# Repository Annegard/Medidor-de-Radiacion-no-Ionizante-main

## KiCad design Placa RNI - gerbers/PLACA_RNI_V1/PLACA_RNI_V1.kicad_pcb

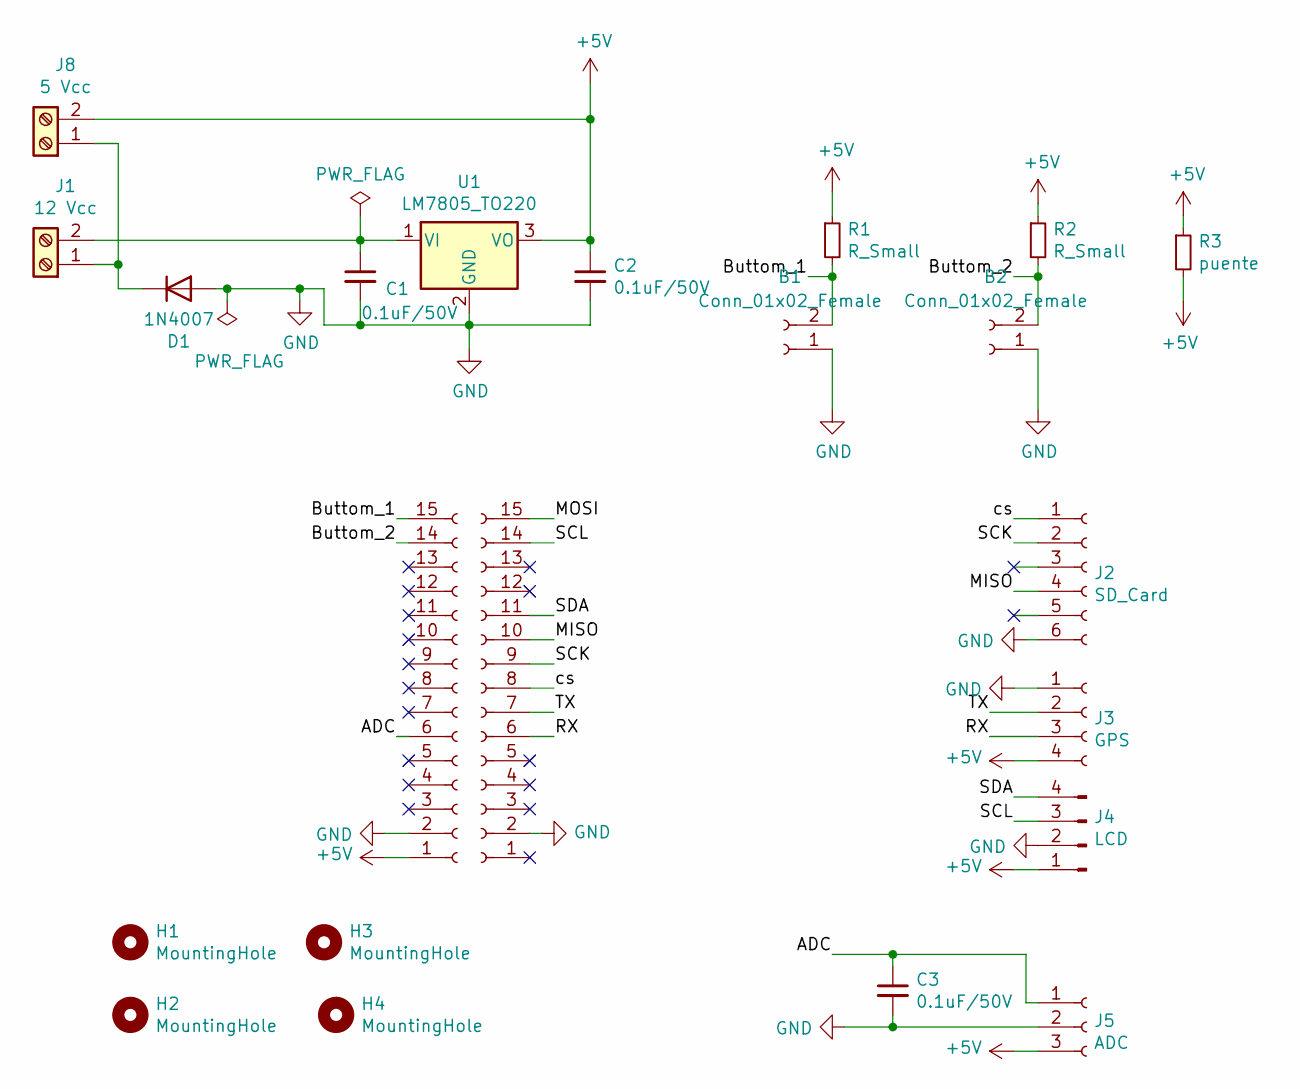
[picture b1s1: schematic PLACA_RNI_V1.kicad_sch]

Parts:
B1, B2: Conn_01x02_Female; PinSocket_1x02_P2.54mm_Vertical
C1, C2, C3: 0.1uF/50V; C_Disc_D7.0mm_W2.5mm_P5.00mm
D1: 1N4007; D_DO-41_SOD81_P10.16mm_Horizontal
H1, H2, H3, H4: MountingHole; MountingHole_2.5mm
J1: 12 Vcc; TerminalBlock_bornier-2_P5.08mm
J2: SD_Card; PinHeader_1x06_P2.54mm_Vertical
J3: GPS; PinHeader_1x04_P2.54mm_Vertical
J4: LCD; PinHeader_1x04_P2.54mm_Vertical
J5: ADC; PinHeader_1x03_P2.54mm_Vertical
J6, J7: Conn_01x15_Female; PinSocket_1x15_P2.54mm_Vertical
J8: 5 Vcc; TerminalBlock_bornier-2_P5.08mm
R1, R2: R_Small; R_Axial_DIN0207_L6.3mm_D2.5mm_P10.16mm_Horizontal
R3: puente; R_Axial_DIN0207_L6.3mm_D2.5mm_P10.16mm_Horizontal
U1: LM7805_TO220; TO-220-3_Vertical

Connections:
+5V: C2.1, J3.4, J4.1, J5.3, J6.1, J8.2, R1.1, R2.1, R3.1, R3.2, U1.3 (VO)
/ADC: C3.1, J5.1, J6.6
/Buttom_1: B1.2, J6.15, R1.2
/Buttom_2: B2.2, J6.14, R2.2
/MISO: J2.4, J7.10
/MOSI: J7.15
/RX: J3.3, J7.6
/SCK: J2.2, J7.9
/SCL: J4.3, J7.14
/SDA: J4.4, J7.11
/TX: J3.2, J7.7
/cs: J2.1, J7.8
GND: B1.1, B2.1, C1.2, C2.2, C3.2, D1.2 (A), J2.6, J3.1, J4.2, J5.2, J6.2, J7.2, U1.2 (GND)
unnamed: C1.1, J1.2, U1.1 (VI)
unnamed: D1.1 (K), J1.1, J8.1

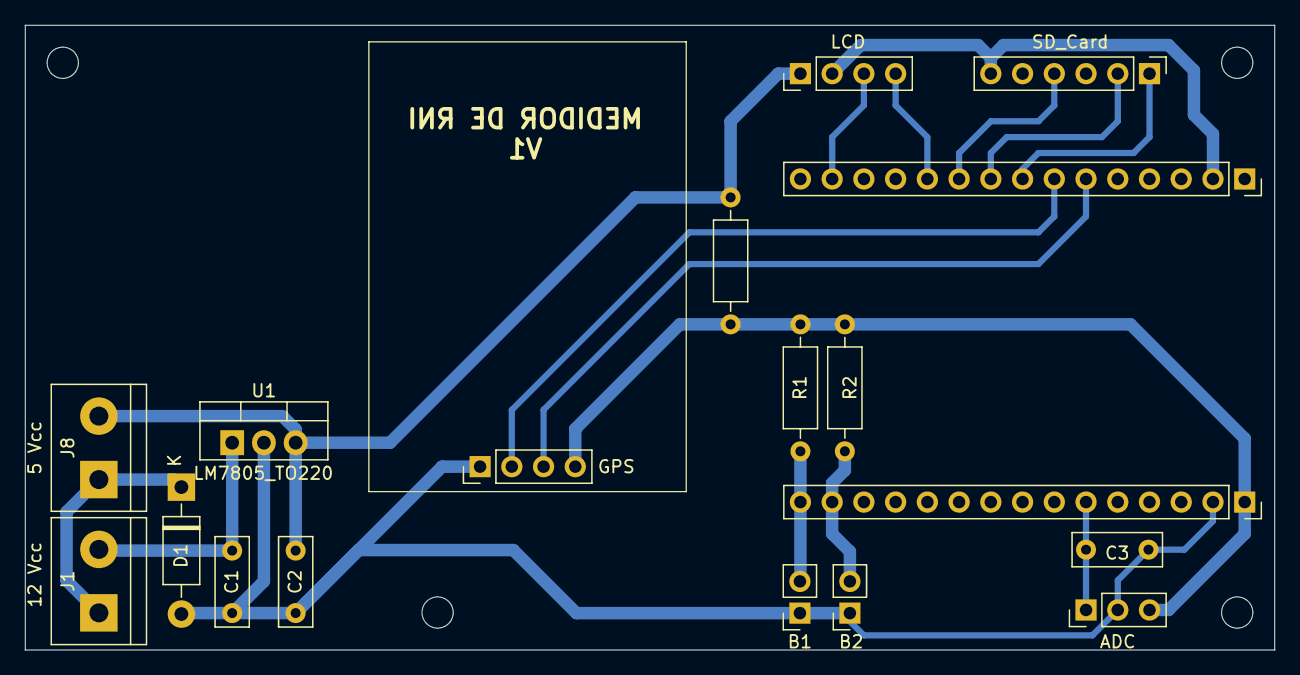
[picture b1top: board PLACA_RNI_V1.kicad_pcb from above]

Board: 2 copper layers, 100.0 x 50.0 mm, 22 parts (0 on the bottom side), 14 nets.

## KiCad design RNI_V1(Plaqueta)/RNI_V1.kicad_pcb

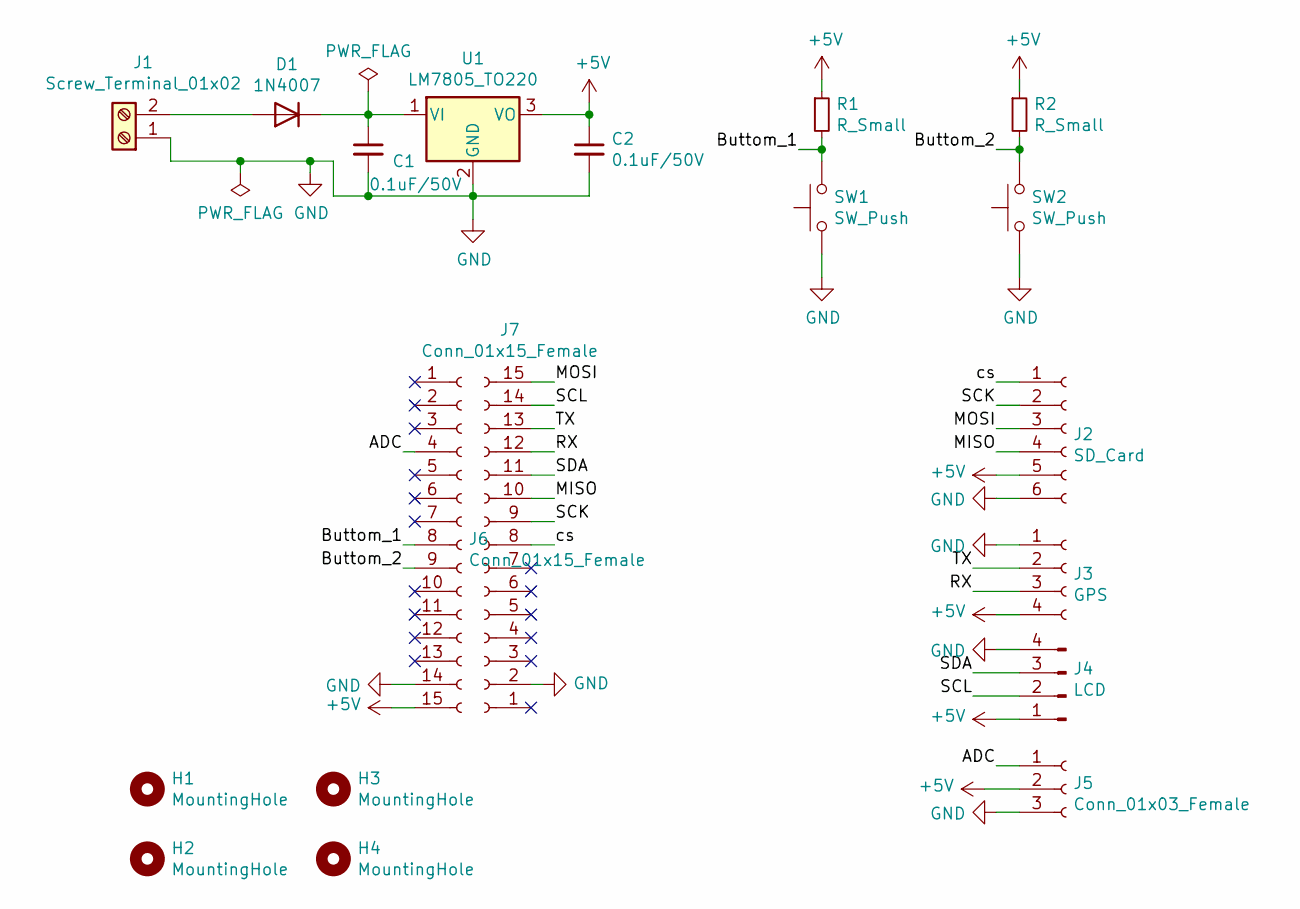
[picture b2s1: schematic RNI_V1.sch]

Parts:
C1, C2: 0.1uF/50V; C_Disc_D7.0mm_W2.5mm_P5.00mm
D1: 1N4007; D_DO-41_SOD81_P10.16mm_Horizontal
H1, H2, H3, H4: MountingHole; MountingHole_5mm
J1: Screw_Terminal_01x02; TerminalBlock_bornier-2_P5.08mm
J2: SD_Card; PinHeader_1x06_P2.54mm_Vertical
J3: GPS; PinHeader_1x04_P2.54mm_Vertical
J4: LCD; PinHeader_1x04_P2.54mm_Vertical
J5: Conn_01x03_Female; PinHeader_1x03_P2.54mm_Vertical
J6, J7: Conn_01x15_Female; PinSocket_1x15_P2.54mm_Vertical
R1, R2: R_Small; R_Axial_DIN0207_L6.3mm_D2.5mm_P10.16mm_Horizontal
SW1, SW2: SW_Push; SW_PUSH_6mm
U1: LM7805_TO220; TO-220-3_Vertical

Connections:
+5V: C2.1, J2.5, J3.4, J4.1, J5.2, J6.15, R1.1, R2.1, U1.3 (VO)
/ADC: J5.1, J6.4
/Buttom_1: J6.8, R1.2, SW1.2
/Buttom_2: J6.9, R2.2, SW2.2
/MISO: J2.4, J7.10
/MOSI: J2.3, J7.15
/RX: J3.3, J7.12
/SCK: J2.2, J7.9
/SCL: J4.2, J7.14
/SDA: J4.3, J7.11
/TX: J3.2, J7.13
/cs: J2.1, J7.8
GND: C1.2, C2.2, J1.1, J2.6, J3.1, J4.4, J5.3, J6.14, J7.2, SW1.1, SW2.1, U1.2 (GND)
unnamed: C1.1, D1.1 (K), U1.1 (VI)
unnamed: D1.2 (A), J1.2

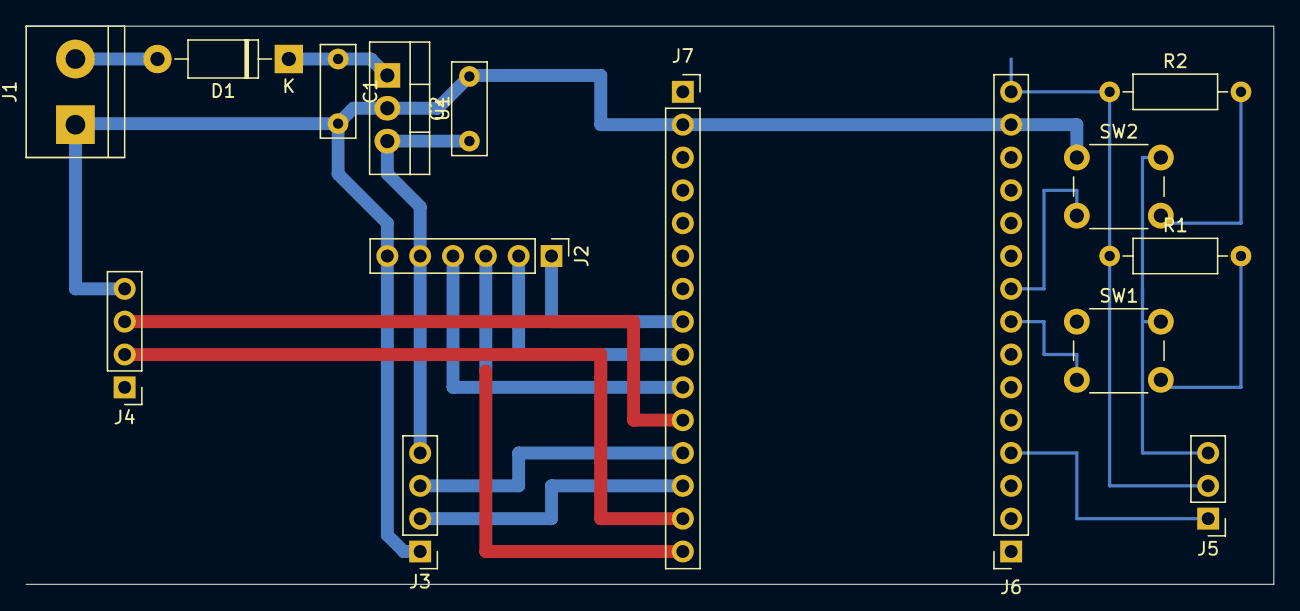
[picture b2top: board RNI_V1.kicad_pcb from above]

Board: 2 copper layers, 96.5 x 43.2 mm, 19 parts (0 on the bottom side), 15 nets.

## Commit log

2022-05-07 subida en modulos
2022-05-07 maquina de estados
2022-05-07 Pulsadores con maquina de Estados
2022-05-07 GASTON CRACK
2022-05-07 MULTITASK
2022-05-07 Freertos_Nuevo
2022-05-08 Subo toda la data del proyecto mas libreria LCD
2022-05-08 LCD libreria mas bibliografia
2022-05-09 cambios en el ACK
2022-08-31 DDDD
2022-08-31 Add files via upload
    Que trolo es el Gaston
2022-08-31 Add files via upload
    Que trolo es gaston parte 2
2022-08-31 Add files via upload
    sin comentarios
2022-09-03 Add files via upload
    Se añade el GPS y el UART
2022-09-04 Correccion de comentarios
2022-09-17 Añado version en Espressif y Arduino
    Ambas versiones cuentan con medidor ADC y GPS, los pulsadores para oscilar entre uno es por interrupcion y no por tareas
2022-12-05 ahi tenes el programa rompe huevos
2023-11-09 carga de datos pertenecientes a gaston
2023-12-18 limpieza y carga de prueba 6
2024-05-12 hola mundo
2024-06-19 carga datos
2024-10-17 añado proyecto 8 con actualizaciones y pruebas en equipo definitivo, faltan SD y WIFI
2024-10-26 actualizo proyecto 8
2024-10-27 actualizo proyecto 8, se habia añadido una libreria erronea, y se crea prueba 9, el cual es una prueba vacia para futuras actualizaciones}
2025-01-13 Carga actualizada con interfaz para seleccionar la red e ingresar la contraseña para subir los datos
